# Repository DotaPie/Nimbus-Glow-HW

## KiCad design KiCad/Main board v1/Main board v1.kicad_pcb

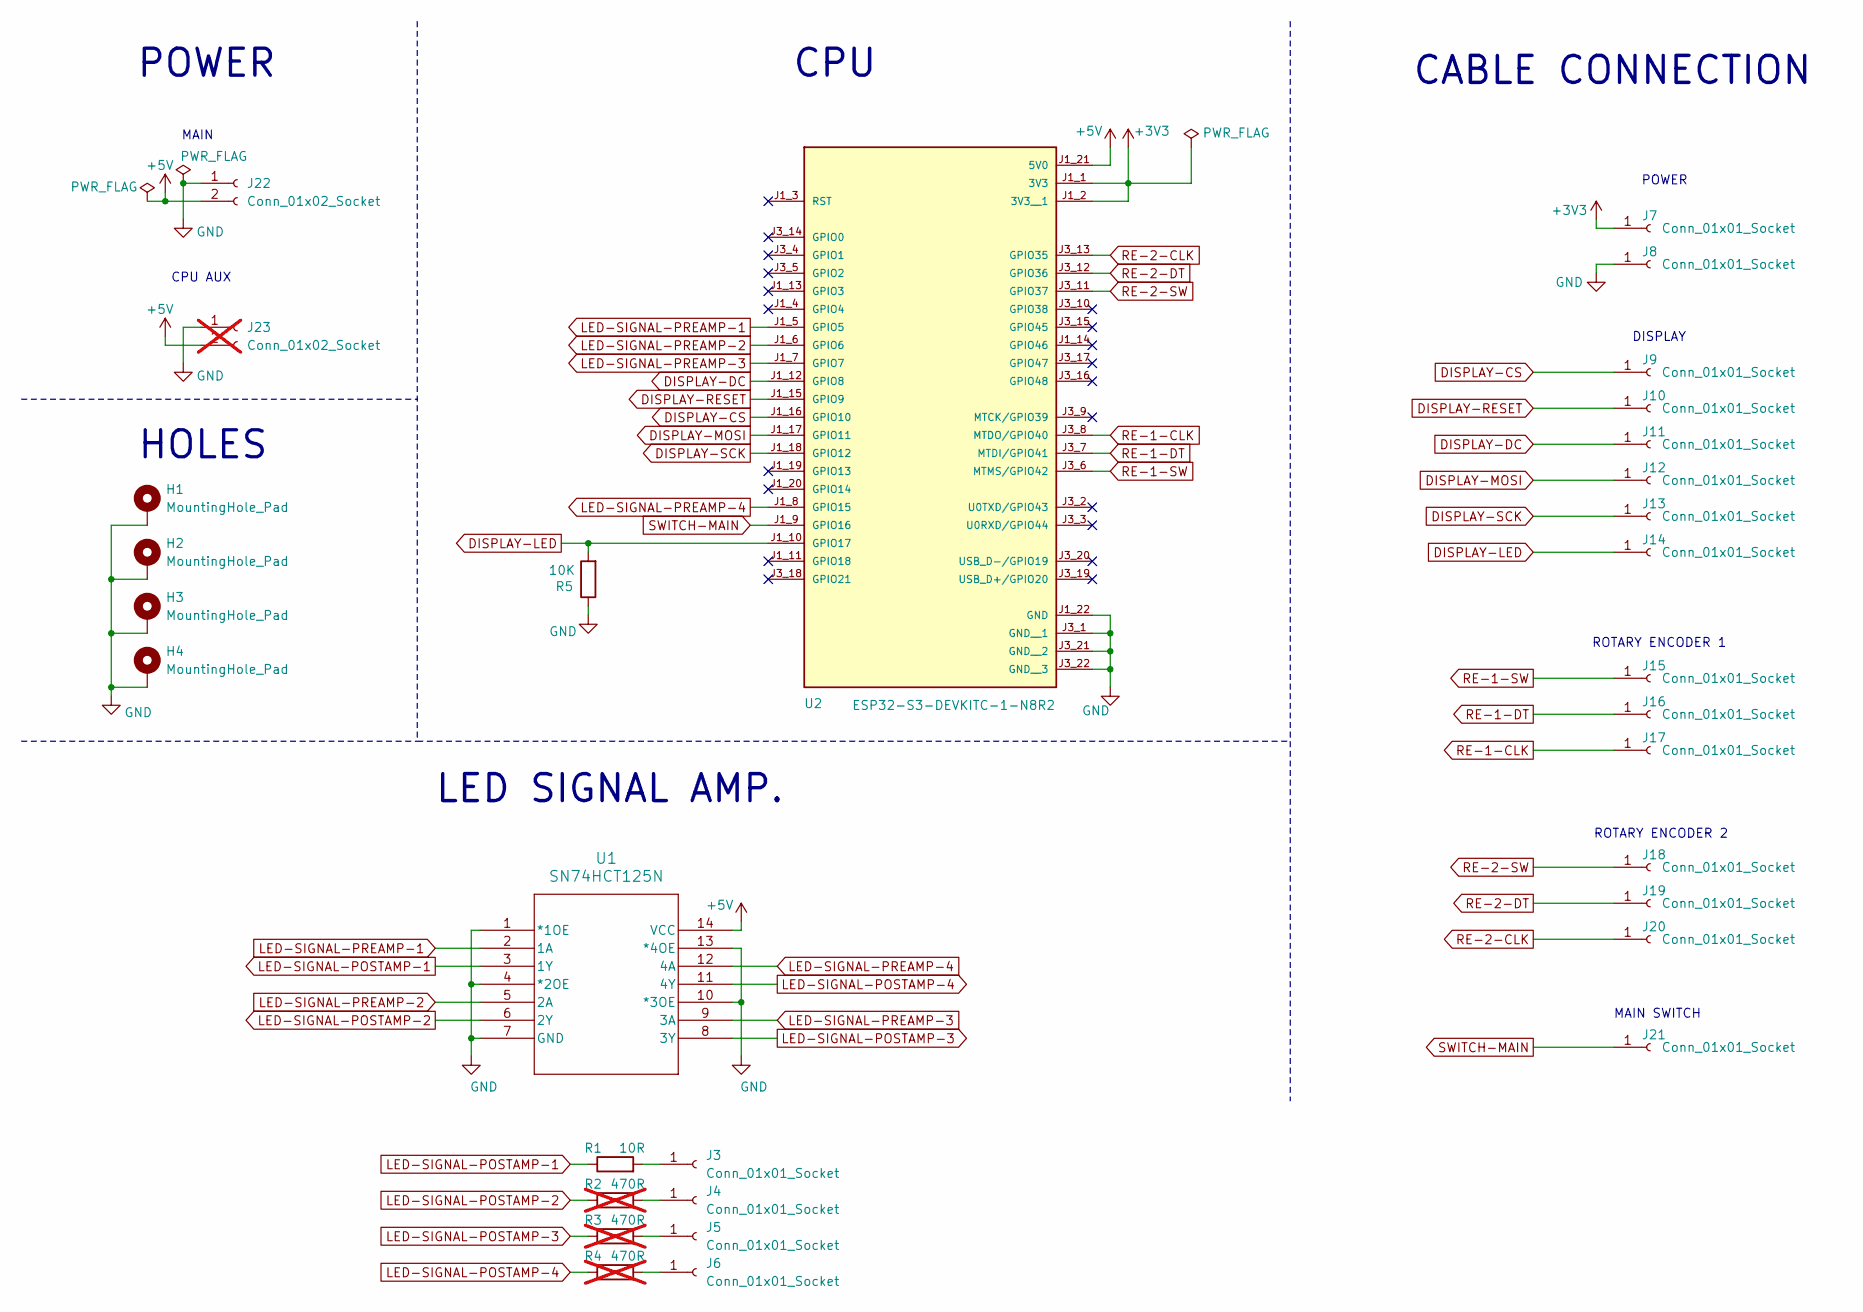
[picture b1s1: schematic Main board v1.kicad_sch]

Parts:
H1, H2, H3, H4: MountingHole_Pad; MountingHole_3.2mm_M3_Pad_TopBottom
J3, J4, J5, J6, J7, J8, J9, J10, J11, J12, J13, J14, J15, J16, J17, J18, J19, J20, J21: Conn_01x01_Socket; TestPoint_Keystone_5019_Miniature
J22: Conn_01x02_Socket; PhoenixContact_MSTBVA_2,5_2-G-5,08_1x02_P5.08mm_Vertical
J23: Conn_01x02_Socket; PhoenixContact_MSTBVA_2,5_2-G-5,08_1x02_P5.08mm_Vertical; not fitted
R1: 10R; R_0805_2012Metric_Pad1.20x1.40mm_HandSolder
R2, R3, R4: 470R; R_0805_2012Metric_Pad1.20x1.40mm_HandSolder; not fitted
R5: 10K; R_0805_2012Metric_Pad1.20x1.40mm_HandSolder
U1: SN74HCT125N; SO-14_3.9x8.65mm_P1.27mm
U2: ESP32-S3-DEVKITC-1-N8R2; XCVR_ESP32-S3-DEVKITC-1-N8R2; PARTREV V1

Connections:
+3V3: J7.1, U2.J1_1 (3V3), U2.J1_2 (3V3__1)
+5V: J22.2, J23.2, U1.14 (VCC), U2.J1_21 (5V0)
DISPLAY-CS: J9.1, U2.J1_16 (GPIO10)
DISPLAY-DC: J11.1, U2.J1_12 (GPIO8)
DISPLAY-LED: J14.1, R5.2, U2.J1_10 (GPIO17)
DISPLAY-MOSI: J12.1, U2.J1_17 (GPIO11)
DISPLAY-RESET: J10.1, U2.J1_15 (GPIO9)
DISPLAY-SCK: J13.1, U2.J1_18 (GPIO12)
GND: H1.1, H2.1, H3.1, H4.1, J8.1, J22.1, J23.1, R5.1, U1.1 (*1OE), U1.4 (*2OE), U1.7 (GND), U1.10 (*3OE), U1.13 (*4OE), U2.J1_22 (GND), U2.J3_1 (GND__1), U2.J3_21 (GND__2), U2.J3_22 (GND__3)
LED-SIGNAL-POSTAMP-1: R1.1, U1.3 (1Y)
LED-SIGNAL-POSTAMP-2: R2.1, U1.6 (2Y)
LED-SIGNAL-POSTAMP-3: R3.1, U1.8 (3Y)
LED-SIGNAL-POSTAMP-4: R4.1, U1.11 (4Y)
LED-SIGNAL-PREAMP-1: U1.2 (1A), U2.J1_5 (GPIO5)
LED-SIGNAL-PREAMP-2: U1.5 (2A), U2.J1_6 (GPIO6)
LED-SIGNAL-PREAMP-3: U1.9 (3A), U2.J1_7 (GPIO7)
LED-SIGNAL-PREAMP-4: U1.12 (4A), U2.J1_8 (GPIO15)
unnamed: J3.1, R1.2
unnamed: J4.1, R2.2
unnamed: J5.1, R3.2
unnamed: J6.1, R4.2
RE-1-CLK: J17.1, U2.J3_8 (MTDO/GPIO40)
RE-1-DT: J16.1, U2.J3_7 (MTDI/GPIO41)
RE-1-SW: J15.1, U2.J3_6 (MTMS/GPIO42)
RE-2-CLK: J20.1, U2.J3_13 (GPIO35)
RE-2-DT: J19.1, U2.J3_12 (GPIO36)
RE-2-SW: J18.1, U2.J3_11 (GPIO37)
SWITCH-MAIN: J21.1, U2.J1_9 (GPIO16)

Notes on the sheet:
CPU AUX
POWER
CABLE CONNECTION
CPU
LED SIGNAL AMP.
ROTARY ENCODER 2
MAIN
DISPLAY
MAIN SWITCH
ROTARY ENCODER 1
HOLES

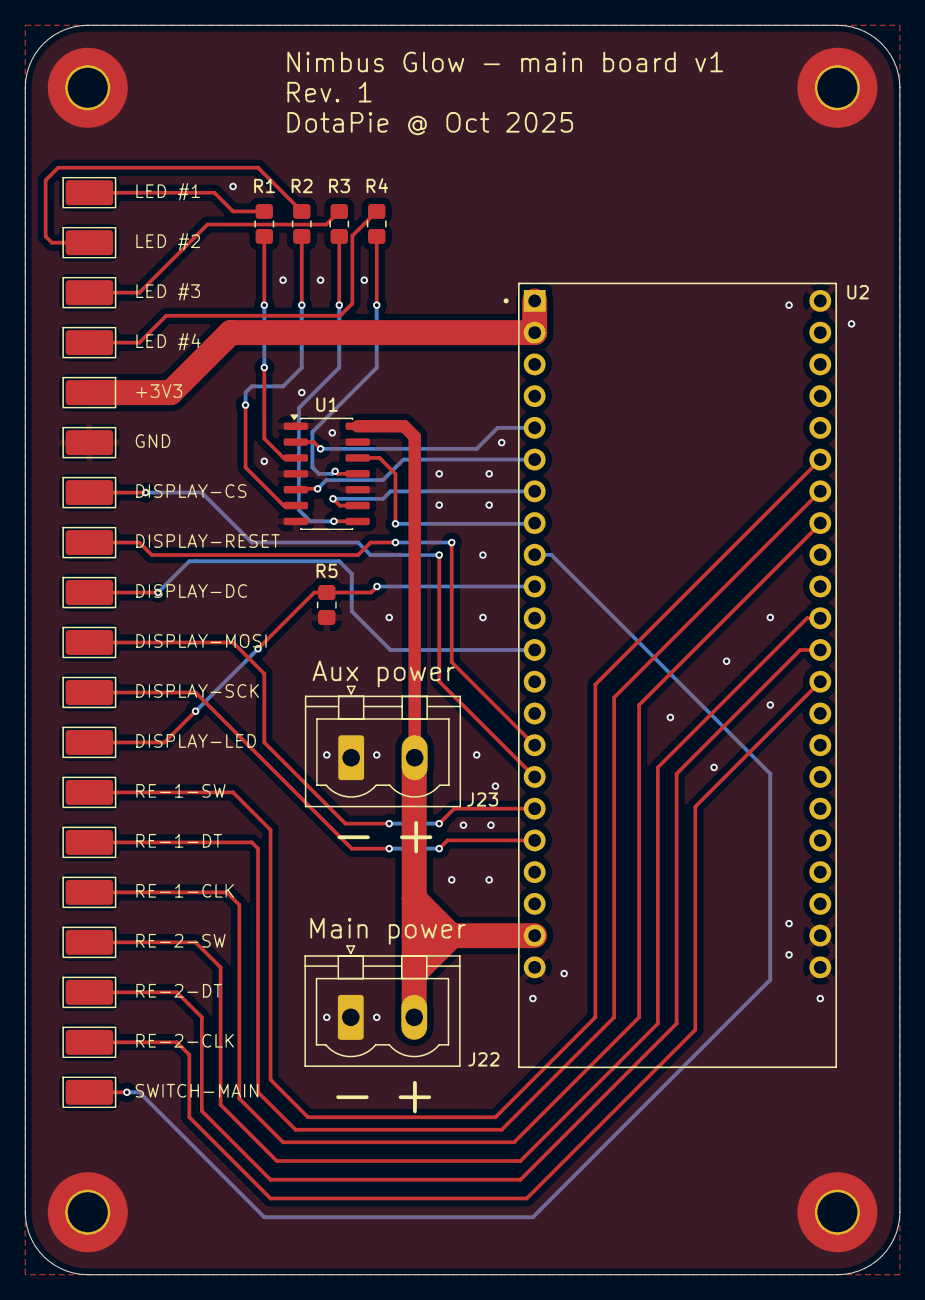
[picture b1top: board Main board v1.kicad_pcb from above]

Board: 2 copper layers, 70.0 x 100.0 mm, 32 parts (0 on the bottom side), 28 nets.

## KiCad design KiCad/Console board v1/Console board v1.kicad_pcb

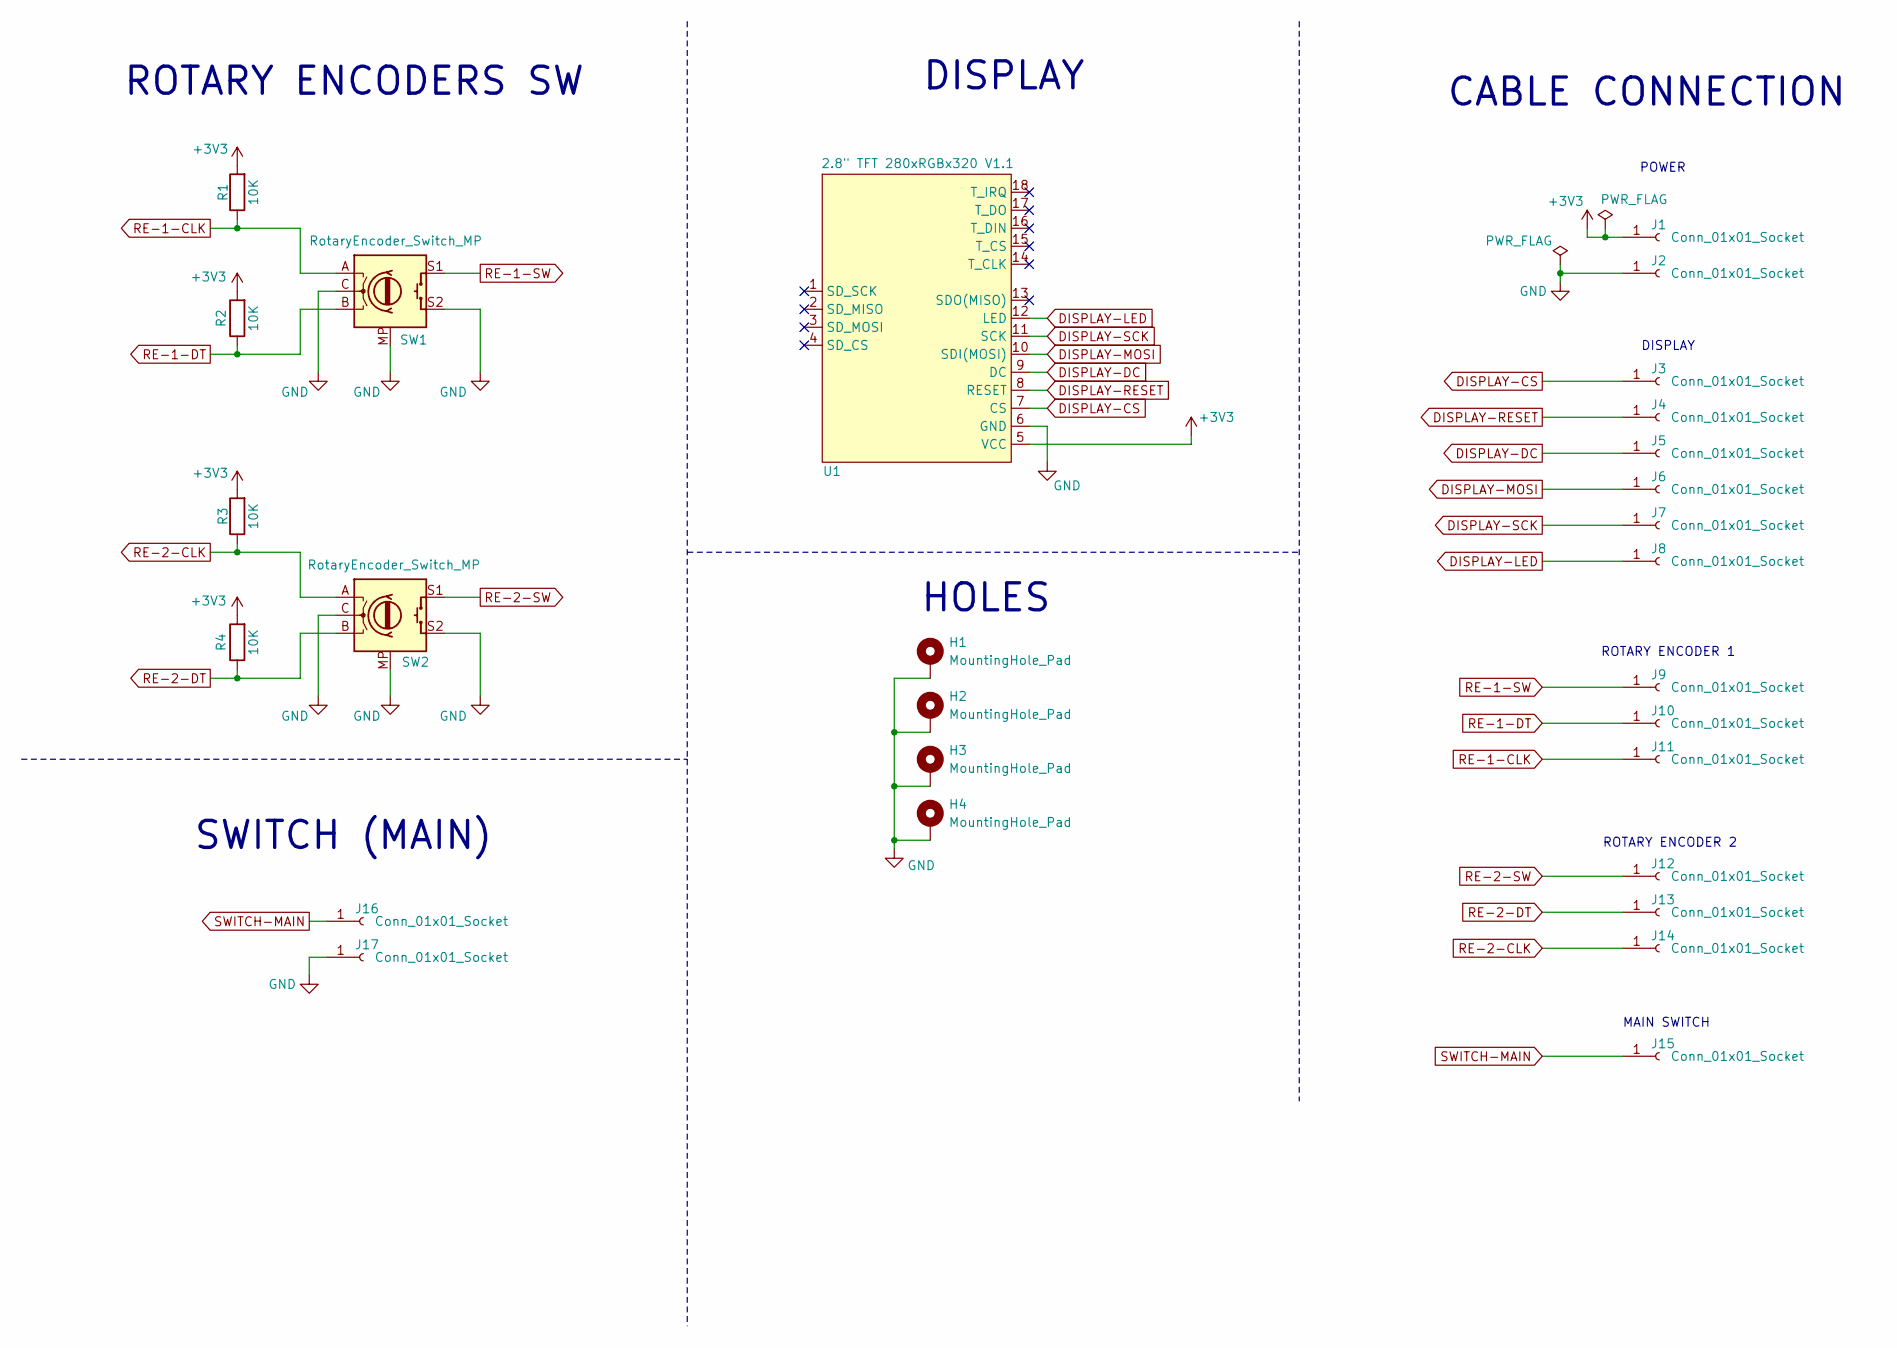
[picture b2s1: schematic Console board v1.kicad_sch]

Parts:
H1, H2, H3, H4: MountingHole_Pad; MountingHole_3.2mm_M3_Pad_TopBottom
J1, J2, J3, J4, J5, J6, J7, J8, J9, J10, J11, J12, J13, J14, J15, J16, J17: Conn_01x01_Socket; TestPoint_Keystone_5019_Miniature
R1, R2, R3, R4: 10K; R_0805_2012Metric_Pad1.20x1.40mm_HandSolder
SW1, SW2: RotaryEncoder_Switch_MP; RotaryEncoder_Alps_EC11E-Switch_Vertical_H20mm
U1: 2.8" TFT 280xRGBx320 V1.1; 2.8 TFT 240xRGBx320

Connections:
+3V3: J1.1, R1.2, R2.2, R3.2, R4.2, U1.5 (VCC)
DISPLAY-CS: J3.1, U1.7 (CS)
DISPLAY-DC: J5.1, U1.9 (DC)
DISPLAY-LED: J8.1, U1.12 (LED)
DISPLAY-MOSI: J6.1, U1.10 (SDI(MOSI))
DISPLAY-RESET: J4.1, U1.8 (RESET)
DISPLAY-SCK: J7.1, U1.11 (SCK)
GND: H1.1, H2.1, H3.1, H4.1, J2.1, J17.1, SW1.C, SW1.MP, SW1.S2, SW2.C, SW2.MP, SW2.S2, U1.6 (GND)
RE-1-CLK: J11.1, R1.1, SW1.A
RE-1-DT: J10.1, R2.1, SW1.B
RE-1-SW: J9.1, SW1.S1
RE-2-CLK: J14.1, R3.1, SW2.A
RE-2-DT: J13.1, R4.1, SW2.B
RE-2-SW: J12.1, SW2.S1
SWITCH-MAIN: J15.1, J16.1

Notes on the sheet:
ROTARY ENCODER 2
DISPLAY
ROTARY ENCODER 1
ROTARY ENCODERS SW
MAIN SWITCH
HOLES
CABLE CONNECTION
POWER
SWITCH (MAIN)

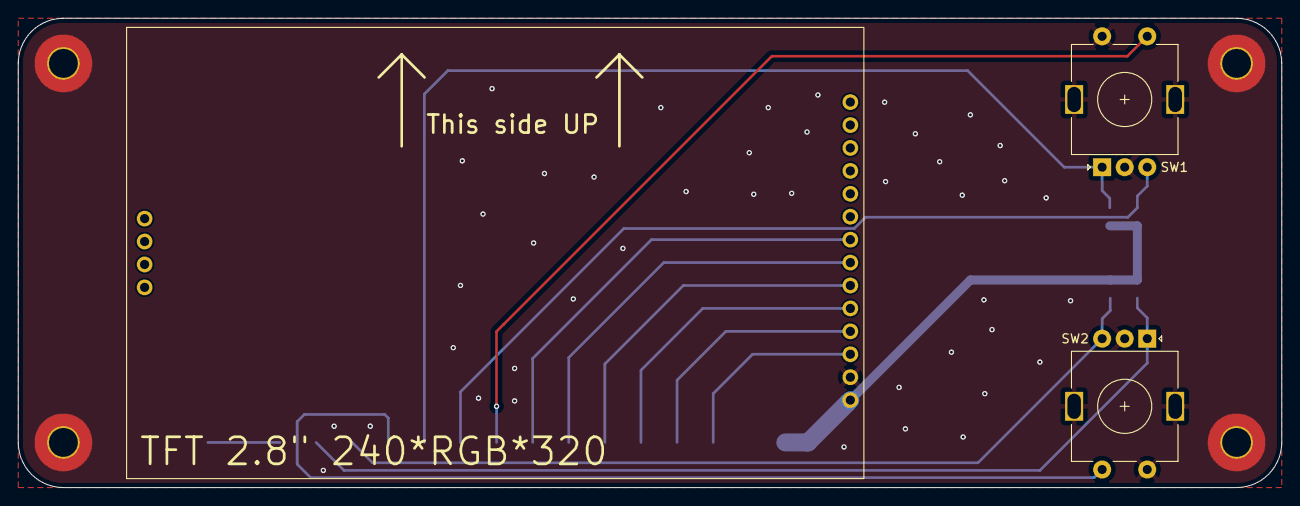
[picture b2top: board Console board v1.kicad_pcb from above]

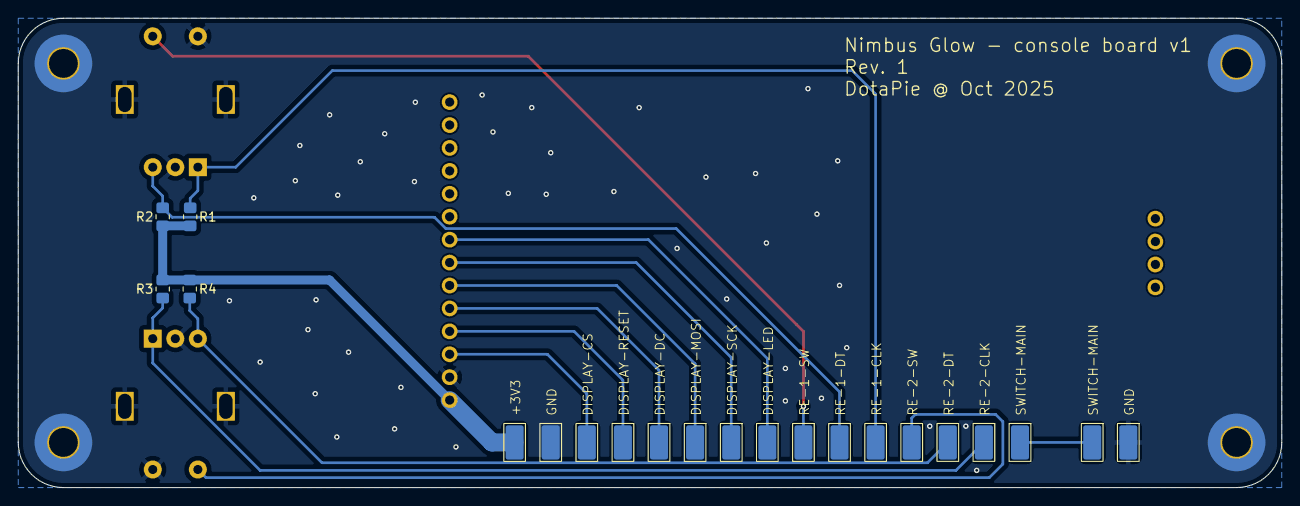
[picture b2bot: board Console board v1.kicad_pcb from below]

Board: 2 copper layers, 140.0 x 52.0 mm, 28 parts (21 on the bottom side), 15 nets.

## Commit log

2025-09-07 Added EUPL 1.2 license
2025-09-07 Init project commit
2025-09-25 restructure
2025-10-07 folder rename
2025-10-23 Scheme and pcb for both boards
2025-10-27 fixes
2025-10-27 JLCPCB exports
2025-11-17 updated JLCPCB exports
